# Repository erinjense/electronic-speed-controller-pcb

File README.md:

# pwmCat-motorBoard

Multidisciplinary Engineering class with requirements of remote-controlled vehicle design to complete "Cat's Conundrum Obstacle Course".
Spring 2018
Montana State University

EAGLE files for PCB for a motor board based on using the atmega328P microcontroller, DRV8833 motor driver, HM-11 Bluetooth LE module, and LSM6DS3TR accel/gyro.  
The atmega328P is used as a finite state machine for direction and speed control.  
The HM-11 receives a byte encoded with direction and speed from an iPhone user.
The atmega328P outputs Pulse-Width-Modulation(PWM) to the DRV8833, receives HM-11 byte via USART and receives accel/gyro data through I2C.
The board uses 3.3V for every device.  
There is a power kill-switch and jumper pin by the ISP1 to separate incoming 5V from other 3.3V devices when programming atmega328P. (TODO: alternative solution).
TODO: 47 uF capacitor as 0805 too small. Some other capacitors sizing needs tweaking.

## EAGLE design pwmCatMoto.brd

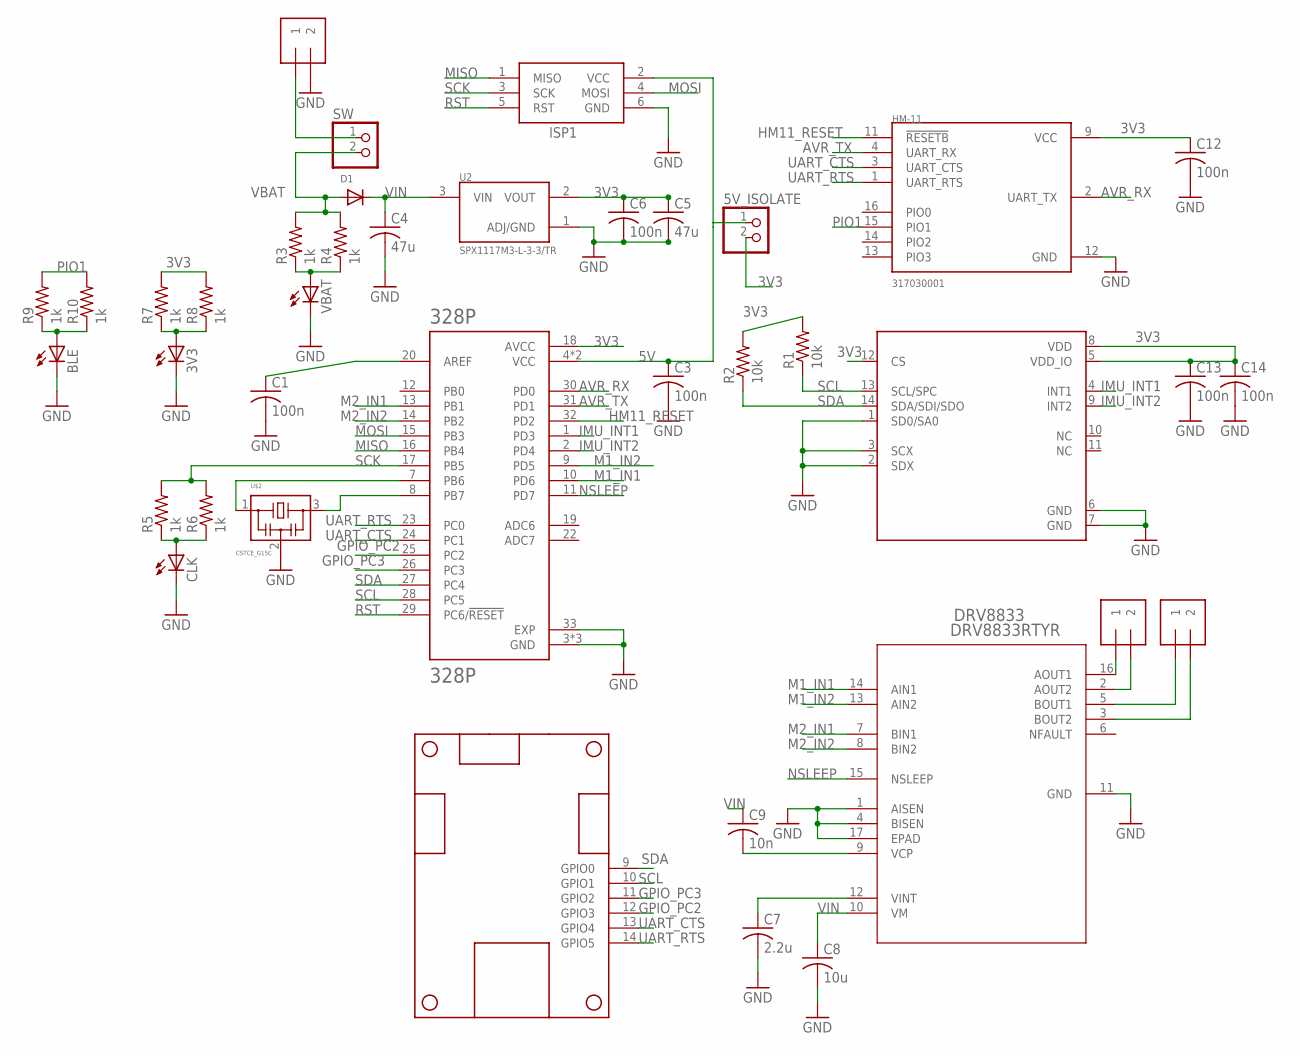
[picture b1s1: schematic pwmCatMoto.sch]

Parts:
3V3: LEDCHIPLED_0805; CHIPLED_0805
5V_ISOLATE: JUMPER; 1X02
328P: 328P; QFN50P500X500X100-33N
ACCEL: LSM6DS3TR; 14VFLGA_LSM6DS3TR
BLE: LEDCHIPLED_0805; CHIPLED_0805
C1, C3, C6, C12, C13, C14: 100n; C0402K
C4, C5: 47u; C0805K
C7: 2.2u; C0402K
C8: 10u; C0402K
C9: 10n; C0402K
CLK: LEDCHIPLED_0805; CHIPLED_0805
D1: DIODESOD-123; SOD-123
DRV8833: DRV8833RTYR; RTY16
HM-11: 317030001; XCVR_317030001
ISP1: AVRISP-6; AVRISP
J4, J5, J6: 1X2-3.5MM
R1, R2: 10k; R0402
R3, R4, R5, R6, R7, R8, R9, R10: 1k; R0402
SW: KILLSWITCH; 1X02
U2: SPX1117M3-L-3-3/TR; SOT230P700X180-3N
U$1: TANK_BOARD_OUTLINE_GPIO; TANK_BOARD_1
U$2: CSTCE_G15C
VBAT: LEDCHIPLED_0805; CHIPLED_0805

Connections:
3V3: 5V_ISOLATE.2, 328P.18 (AVCC), ACCEL.5 (VDD_IO), ACCEL.8 (VDD), ACCEL.12 (CS), C5.1, C6.1, C12.1, C13.1, C14.1, HM-11.9 (VCC), R1.2, R2.2, R7.2, R8.2, U2.2 (VOUT)
5V: 5V_ISOLATE.1, 328P.4 (VCC), 328P.6 (VCC), C3.1, ISP1.2 (VCC)
AVR_RX: 328P.30 (PD0), HM-11.2 (UART_TX)
AVR_TX: 328P.31 (PD1), HM-11.4 (UART_RX)
GND: 3V3.C, 328P.3 (GND), 328P.5 (GND), 328P.21 (GND), 328P.33 (EXP), ACCEL.1 (SD0/SA0), ACCEL.2 (SDX), ACCEL.3 (SCX), ACCEL.6 (GND), ACCEL.7 (GND), BLE.C, C1.2, C3.2, C4.2, C5.2, C6.2, C7.2, C8.2, C12.2, C13.2, C14.2, CLK.C, DRV8833.1 (AISEN), DRV8833.4 (BISEN), DRV8833.11 (GND), DRV8833.17 (EPAD), HM-11.12 (GND), ISP1.6 (GND), J4.2, U2.1 (ADJ/GND), U$2.2, VBAT.C
GPIO_PC2: 328P.25 (PC2), U$1.12 (GPIO3)
GPIO_PC3: 328P.26 (PC3), U$1.11 (GPIO2)
HM11_RESET: 328P.32 (PD2), HM-11.11 (!RESETB)
IMU_INT1: 328P.1 (PD3), ACCEL.4 (INT1)
IMU_INT2: 328P.2 (PD4), ACCEL.9 (INT2)
M1_IN1: 328P.10 (PD6), DRV8833.14 (AIN1)
M1_IN2: 328P.9 (PD5), DRV8833.13 (AIN2)
M2_IN1: 328P.13 (PB1), DRV8833.7 (BIN1)
M2_IN2: 328P.14 (PB2), DRV8833.8 (BIN2)
MISO: 328P.16 (PB4), ISP1.1 (MISO)
MOSI: 328P.15 (PB3), ISP1.4 (MOSI)
unnamed: C7.1, DRV8833.12 (VINT)
unnamed: 328P.7 (PB6), U$2.1
unnamed: 328P.8 (PB7), U$2.3
unnamed: 328P.20 (AREF), C1.1
unnamed: C9.2, DRV8833.9 (VCP)
unnamed: J4.1, SW.1
unnamed: R3.1, R4.1, VBAT.A
unnamed: BLE.A, R9.1, R10.1
unnamed: CLK.A, R5.1, R6.1
unnamed: 3V3.A, R7.1, R8.1
unnamed: DRV8833.16 (AOUT1), J5.1
unnamed: DRV8833.2 (AOUT2), J5.2
unnamed: DRV8833.5 (BOUT1), J6.1
unnamed: DRV8833.3 (BOUT2), J6.2
NC: ACCEL.10 (NC), ACCEL.11 (NC)
NSLEEP: 328P.11 (PD7), DRV8833.15 (NSLEEP)
PIO1: HM-11.15 (PIO1), R9.2, R10.2
RST: 328P.29 (PC6/!RESET), ISP1.5 (RST)
SCK: 328P.17 (PB5), ISP1.3 (SCK), R5.2, R6.2
SCL: 328P.28 (PC5), ACCEL.13 (SCL/SPC), R1.1, U$1.10 (GPIO1)
SDA: 328P.27 (PC4), ACCEL.14 (SDA/SDI/SDO), R2.1, U$1.9 (GPIO0)
UART_CTS: 328P.24 (PC1), HM-11.3 (UART_CTS), U$1.13 (GPIO4)
UART_RTS: 328P.23 (PC0), HM-11.1 (UART_RTS), U$1.14 (GPIO5)
VBAT: D1.A, R3.2, R4.2, SW.2
VIN: C4.1, C8.1, C9.1, D1.C, DRV8833.10 (VM), U2.3 (VIN)

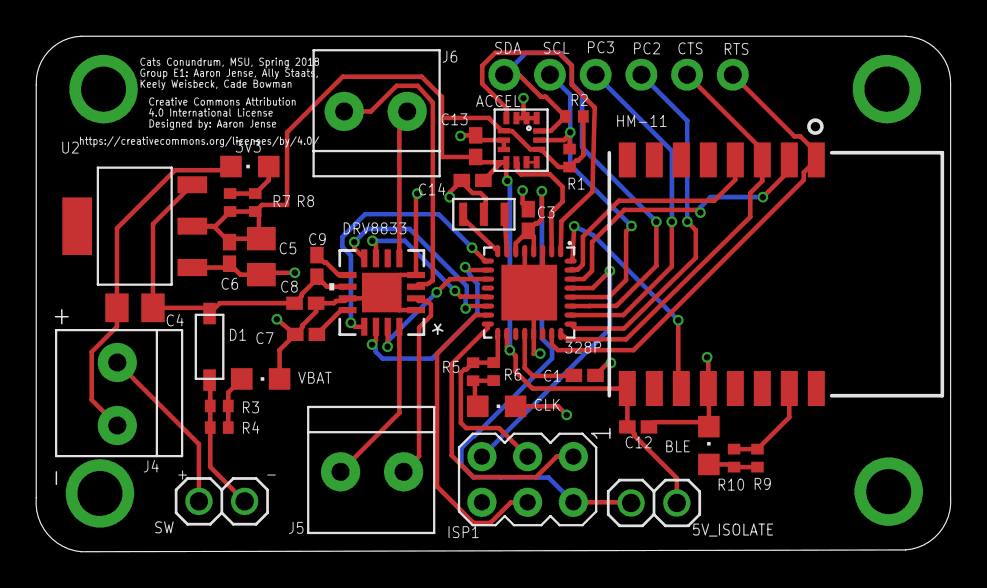
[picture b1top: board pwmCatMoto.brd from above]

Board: 2 copper layers, 50.8 x 28.6 mm, 39 parts (0 on the bottom side), 41 nets.

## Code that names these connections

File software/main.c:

/* Direction and Speed Finite State Machine
 *
 * Designed for pwmCat-motorBoard
 *
 * Receives a Bluetooth Low Energy (BLE) signal
 * from an iPhone app or any other BLE capable device
 * connected and transmiting the correct ASCII letter/number.
 *
 * Code was designed for discrete signals. e.g. ( The user
 * presses a forward arrow on an app. The app sends 'F' to 
 * the BLE module on motor board. The atmega328p receives
 * signal from the BLE module via UART.
 * This code then drives motors to go in a forward direction.
 * The code will remain in forward direction unless the user
 * changes direction.)
 *
 * DIRECTION SIGNALS:
 *
 * forward: 'F'
 * backward: 'B'
 * right: 'R'
 * left: 'L'
 *
 * SPEED SIGNALS:
 *
 * stop : '0'
 * slow : '1'
 * mid : '2'
 * max : '3'
 *
 */


#include <avr/io.h>
#include <avr/interrupt.h>
#include "pinDefines.h"
#include <util/delay.h>
#include "USART.h"
#include "PWM.h"

#define UBRR_VALUE (((F_CPU / (USART_BAUDRATE * 16UL))) - 1)
#define USART_BAUDRATE 9600

/* Delays so that the motors don't instantly go from max speed
 * to stop or change direction instatnly at high speeds.
 * This helps prevent current spikes
 */
#define MOTOR_SYNC_DELAY 5
#define SPEED_STEP_DELAY 2

#define MAX_SPEED 50
#define MED_SPEED 100
#define SLOW_SPEED 191
#define STOP_SPEED 255
#define SAFE_SPEED 150

/* Changes speed in steps with safety delays */
void change_speed(uint8_t new_speed) {

  while (OCR0A != new_speed) {
    if (OCR0A < new_speed) { 
      OCR0A++; 
      OCR0B = OCR0A; 
      OCR1A = OCR0A;
      OCR1B = OCR0A;
      _delay_ms(SPEED_STEP_DELAY);
    }
    else if (OCR0A > new_speed) { 
      OCR0A--; 
      OCR0B = OCR0A; 
      OCR1A = OCR0A;
      OCR1B = OCR0A;
      _delay_ms(SPEED_STEP_DELAY);
    }
  }

}
int main(void) {
  uint8_t rx_byte;
  uint8_t current_speed;
  uint8_t last_speed;
  /* Data Direction inits for PortB and PortD */
  DDRB |= ((1 << PB1) | (1 << PB2) | (1 << PB5));
  DDRD |= ((1 << PD2) | (1 << PD5) | (1 << PD6) | (1 << PD7));
  /* nSleep ON for DRV8833 = motor output ON */
  PORTD |= (1 << PD7);

  initPWM();
  initUSART();

  current_speed = 150;
  last_speed = current_speed;

  OCR0A = current_speed;
  OCR0B = OCR0A;
  OCR1A = OCR0A;
  OCR1B = OCR0A;

  printString("AT+NAMEpwmCat");

  while(1) {

    /* No user-signal, STOP the motors
     * This would be handy if user control app
     * continuously sends a signal if user
     * continuously holds down a button, but
     * the motors need to stop if user is not
     * sending a signal.
     */
   /* 
    if ( (UCSR0A & 0b10000000) == 0b00000000) {
      change_speed(STOP_SPEED);  
    }
    */

    // Wait forever until user-signal and get it
    rx_byte = receiveByte();

    switch (rx_byte) {

      // Forward
      case 'F':

        /* Always enable motor driver. In case user is
         * going from stop and then changed direction */
        PORTD |= (1 << PD7);

        if (current_speed == STOP_SPEED) {
          forwardPWM();
          current_speed = last_speed;
          change_speed(current_speed);
        }
        /* max speed is 0 and min speed is 255
         * This checks to see if current speed 
         * is higher than a safe speed.
         * The comparison operators are non-intuitive
         */
        else if (current_speed < SAFE_SPEED) {
          change_speed(SAFE_SPEED);
          forwardPWM();
          change_speed(current_speed);
        }
        else { forwardPWM(); }
        break;

      // Backward
      case 'B':
        PORTD |= (1 << PD7);
        if (current_speed == STOP_SPEED) {
          reversePWM();
          current_speed = last_speed;
          change_speed(current_speed);
        }
        else if (current_speed < SAFE_SPEED) {
          change_speed(SAFE_SPEED);
          reversePWM();
          change_speed(current_speed);
        }
        else { reversePWM(); }
        break;

      // Right
      case 'R':
        PORTD |= (1 << PD7);
        if (current_speed == STOP_SPEED) {
          rightPWM();
          current_speed = last_speed;
          change_speed(current_speed);
        }
        else if (current_speed < SAFE_SPEED) {
          change_speed(SAFE_SPEED);
          rightPWM();
          change_speed(current_speed);
        }
        else { rightPWM(); }
        break;
      // Left
      case 'L':
        PORTD |= (1 << PD7);
        if (current_speed == STOP_SPEED) {
          leftPWM();
          current_speed = last_speed;
          change_speed(current_speed);
        }
        else if (current_speed < SAFE_SPEED) {
          change_speed(SAFE_SPEED);
          leftPWM();
          change_speed(current_speed);
        }
        else { leftPWM(); }
        break;
    }

    // Change Speed State
    switch(rx_byte) {

      // Stop
      case '0':
        /* Disable motor driver output */
        PORTD &= ~(1 << PD7);
        /* keep track of last speed, so that
         * if user pressed stop and then changes
         * direction. Then last speed remains same.*/
        last_speed = current_speed;
        current_speed = STOP_SPEED;
        change_speed(current_speed); 
        break;
      // Slowest
      case '1':
        current_speed = SLOW_SPEED;
        change_speed(current_speed);
        break;
      // Medium
      case '2':
        current_speed = MED_SPEED;
        change_speed(current_speed); 
        break;
      // Fastest
      case '3':
        current_speed = MAX_SPEED;
        change_speed(current_speed); 
        break;
    }

  }
  /* Code never reaches here */
  return(0);
}

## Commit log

2018-02-25 proto1-nonVerified
2018-02-25 Documentation
2018-02-25 format
2020-10-22 Merged seperate software repository into hardware repository.

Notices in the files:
pwmCatMoto.brd:
Creative Commons Attribution
https://creativecommons.org/licenses/by/4.0
